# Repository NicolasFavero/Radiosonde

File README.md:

# Radiossonda Experimental (v2.0)

## Sobre o projeto

A **versão 2.0** consiste no desenvolvimento de uma plataforma embarcada para uma **radiossonda experimental**, destinada à aquisição e transmissão de dados ambientais durante voos em balões de alta altitude.

O sistema é baseado em um **ESP32-S3 Supermini** e possui uma arquitetura modular, permitindo a utilização de diferentes módulos de rádio através da mesma PCB, tornando a plataforma flexível para diferentes aplicações e faixas de frequência.

Além da telemetria, a placa oferece interfaces para sensores e módulos opcionais, permitindo sua adaptação para diferentes experimentos científicos e educacionais.

---

# Objetivos

Desenvolver uma plataforma compacta para aquisição e transmissão de dados ambientais, integrando:

- Localização por GPS;
- Medição de pressão e altitude;
- Comunicação via rádio;
- Alimentação para diferentes configurações de bateria;
- Arquitetura preparada para futuras expansões.

---

# Funcionalidades

## Comunicação

- Suporte para múltiplas famílias de rádios;
- Comunicação LoRa e FSK;
- Compatibilidade com diferentes módulos sem necessidade de uma nova PCB.

## Sensoriamento

- Interface para módulo GPS;
- Barramento I²C para sensores adicionais;
- Suporte opcional ao conversor MAX31865 para sensores RTD.

## Alimentação

- Alimentação por baterias Li-Ion/LiPo de **1S até 3S**;
- Conversor Buck-Boost integrado;
- Conector dedicado para bateria.

---

# Status do projeto

🚧 **Em desenvolvimento**

O hardware e o firmware encontram-se em constante evolução, podendo receber novos sensores, módulos de rádio e funcionalidades.

---

# Hardware

- ESP32-S3 Supermini;
- Conversor Buck-Boost;
- Conector para bateria;
- Barramento I²C;
- Suporte para módulo GPS;
- Suporte opcional ao MAX31865;
- Até dois conectores SMA;
- PCB dedicada.

---

# Software

- C++;
- PlatformIO;
- Arduino Framework.

---

# Ambiente de Desenvolvimento

- IDE: PlatformIO;
- Framework: Arduino;
- Placa alvo: ESP32-S3.

---

# Estrutura do Projeto

```text
Firmware/
├── include/
├── lib/
├── src/
└── platformio.ini

Hardware/
├── PCB/
└── Documentação/
```

---

# Aplicação

Projeto desenvolvido para fins educacionais e experimentais, servindo como plataforma para estudos de telemetria, sensoriamento ambiental, comunicação por rádio e sistemas embarcados aplicados a radiossondas.

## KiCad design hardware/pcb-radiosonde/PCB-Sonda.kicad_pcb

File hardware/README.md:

# Hardware

Esta pasta contém os esquemáticos, layouts e demais arquivos relacionados à PCB da **Radiossonda Experimental v2.0**.

A placa foi projetada para oferecer uma plataforma compacta e flexível, permitindo a utilização de diferentes módulos de rádio através da mesma PCB.

---

# Microcontrolador

- ESP32-S3 Supermini

---

# Comunicação por Rádio

A PCB suporta diferentes módulos de rádio.

## Instalação direta

- RF96W;
- RFM95;
- RFM96;
- Outros módulos compatíveis com a mesma pinagem.

## Instalação alternativa

Através da configuração de pads de solda, a PCB também pode utilizar um dos seguintes módulos:

- Módulos baseados no **Semtech LLCC68** (como os modelos da NiceRF);
- **EBYTE E07-M1101D** (formato ESP-01);
- RFM69W.

Essa abordagem permite reutilizar a mesma PCB para diferentes tecnologias e bandas de operação.

---

# Alimentação

A placa possui:

- Conversor Buck-Boost integrado;
- Alimentação por baterias Li-Ion/LiPo de **1S até 3S**;
- Conector dedicado para bateria.

---

# Sensores e Expansões

A PCB disponibiliza:

- Barramento I²C para conexão de sensores, como o BMP280;
- Suporte para módulo GPS;
- Suporte opcional ao conversor **MAX31865** para sensores RTD;
- Conector I²C para expansão de outros periféricos.

Os módulos GPS e MAX31865 podem ser montados na região lateral da placa, permanecendo parcialmente externos ao contorno principal da PCB para otimizar o aproveitamento de espaço.

---

# Antenas

A placa possui suporte para até **2 conectores SMA**, permitindo diferentes configurações de antenas conforme a aplicação.

---

# Estrutura

```text
Hardware/
└── PCB/
```

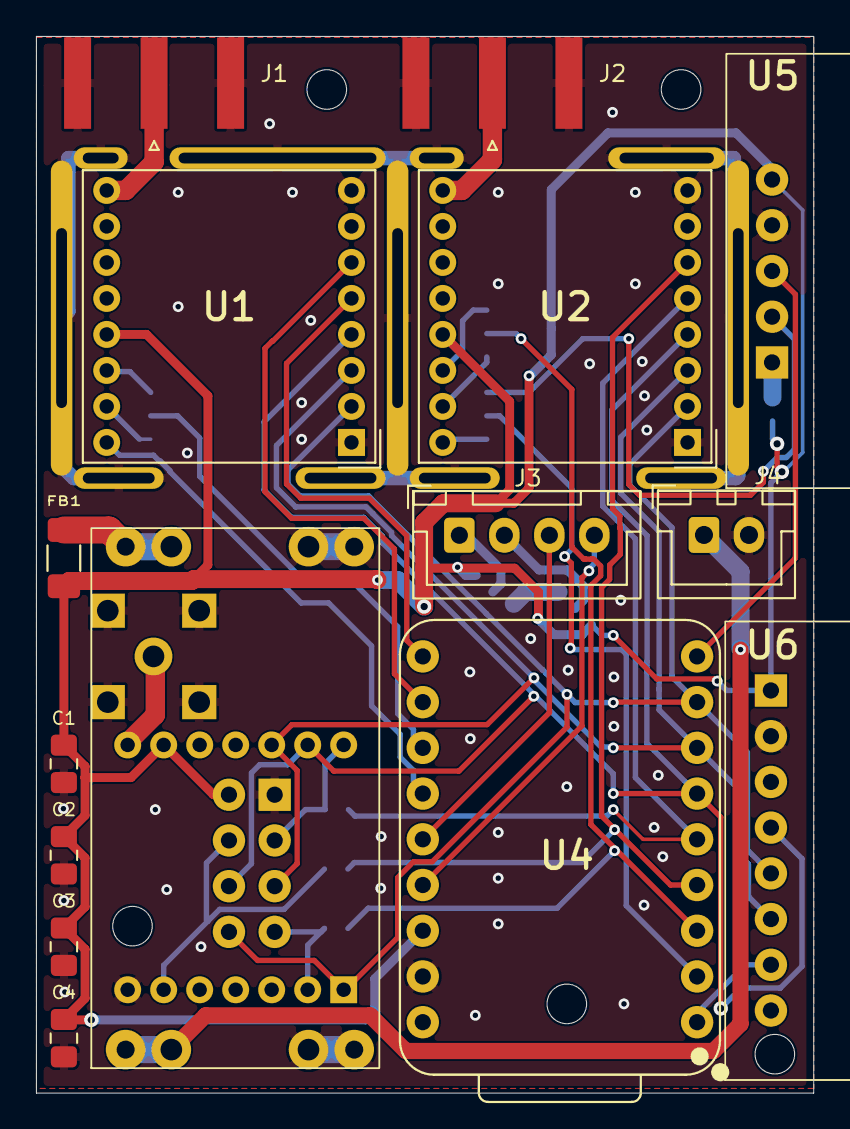
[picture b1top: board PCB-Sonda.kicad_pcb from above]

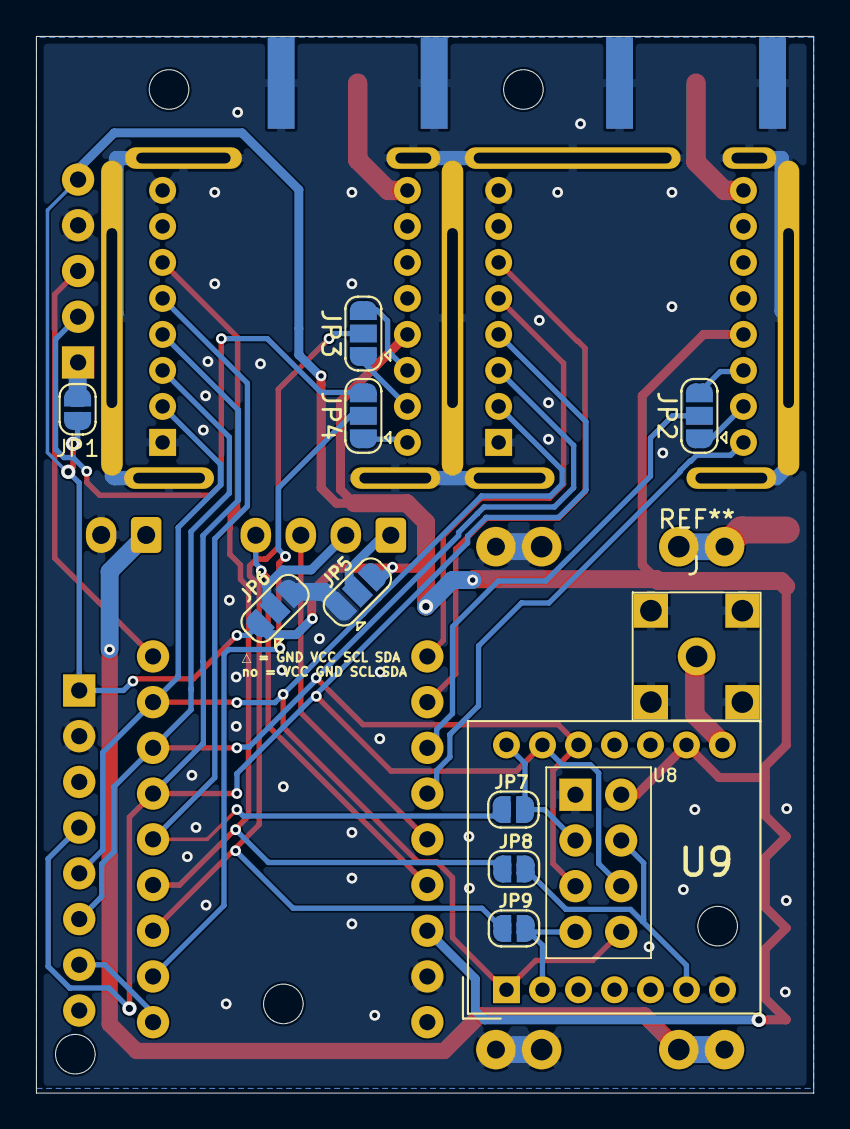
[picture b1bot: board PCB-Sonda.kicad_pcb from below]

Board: 2 copper layers, 43.2 x 58.7 mm, 26 parts (11 on the bottom side), 33 nets.

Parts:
C1, C2: 100nF; C_0805_2012Metric_Pad1.18x1.45mm_HandSolder
C3: 1uF; C_0805_2012Metric_Pad1.18x1.45mm_HandSolder
C4: 1000uF; C_0805_2012Metric_Pad1.18x1.45mm_HandSolder
FB1: 120R; C_1206_3216Metric_Pad1.33x1.80mm_HandSolder
J1, J2: ANT; SMA_Amphenol_132289_EdgeMount
J3: JST; JST_XH_B4B-XH-A_1x04_P2.50mm_Vertical
J4: JST; JST_XH_B2B-XH-A_1x02_P2.50mm_Vertical
JP1, JP7, JP8, JP9: SolderJumper_2_Open; SolderJumper-2_P1.3mm_Open_RoundedPad1.0x1.5mm
JP2, JP3, JP4, JP5, JP6: SolderJumper_3_Open; SolderJumper-3_P1.3mm_Open_RoundedPad1.0x1.5mm
U1: RF96W; rf96w
U2: CC68; rf96w
U3: TPS63070
U4: ESP32-S3-SUPERMIINI; myEsp32-S3-Mini
U5: GPS(black); GPS-PretoComPPS
U6: MAX31865
U8: E07-M11010; Radio-Esp01
U9: RFM69C; rfm69c

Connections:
+3.3V: C1.1, C2.1, C3.1, C4.1, FB1.2, JP1.2 (B), JP5.3 (B), JP6.1 (A), U1.13 (3V3), U2.13 (3V3), U4.16 (VCC_3V3), U5.5 (VCC), U6.1 (VCC), U8.2 (VCC), U9.9 (3V3)
+3.3VA: FB1.1, U3.3 (VOUT)
BUSY-CC68: JP4.1 (A), U2.16 (DIO2/BUSY)
BUSY-RF96W: U1.16 (DIO2/BUSY), U4.13 (GPIO11)
CLK: U1.4 (SCK), U2.4 (SCK), U4.6 (GPIO4), U6.4 (CLK), U8.6 (CLK), U9.13 (SCK)
CS-CC68: JP7.1 (A), U2.5 (NSS), U4.5 (GPIO3)
CS-E07M11010: JP7.2 (B), U8.3 (NSS), U9.14 (NSS)
CS-MAX31865: U4.1 (TX), U6.7 (CS)
CS-RF96W: U1.5 (NSS), U4.10 (GPIO8)
DIO0-CC68: JP3.3 (B), U2.14 (DIO0)
DIO0-E07M11010: JP9.1 (A), U8.7 (DIO0), U9.2 (DIO0)
DIO0-RF96W: JP2.3 (B), U1.14 (DIO0)
DIO0e1-CC68: JP3.2 (C), JP9.2 (B), U4.3 (GPIO1/D0/A0)
DIO0e1-RF96W: JP2.2 (C), U4.12 (GPIO10)
DIO1-CC68: JP3.1 (A), U2.15 (DIO1)
DIO1-RF96W: JP2.1 (A), U1.15 (DIO1)
GND: C1.2, C2.2, C3.2, C4.2, J1.2 (GND), J2.2 (GND), J4.2 (BAT-), JP5.1 (A), JP6.3 (B), U1.1 (GND), U1.8 (GND), U2.1 (GND), U2.8 (GND), U3.1 (GND), U3.4 (GND), U4.17 (GND), U5.4 (GND), U6.2 (GND), U8.1 (GND), U9.7 (GND)
MISO: U1.2 (MISO), U2.2 (MISO), U4.8 (GPIO6), U6.5 (MISO), U8.8 (MISO), U9.1 (MISO)
MOSI: U1.3 (MOSI), U2.3 (MOSI), U4.7 (GPIO5), U6.6 (MOSI), U8.5 (MOSI), U9.12 (MOSI)
unnamed: J1.1 (ANT), U1.9 (ANT)
unnamed: J2.1 (ANT), U2.9 (ANT)
unnamed: J3.2 (GND), JP6.2 (C)
unnamed: J3.1 (VCC), JP5.2 (C)
unnamed: J4.1 (BAT+), U3.2 (VIN)
unnamed: JP1.1 (A), U5.1 (PPS)
RESET-RFM69C: JP8.2 (B), U8.4 (RST), U9.6 (RESET)
RST-CC68: JP8.1 (A), U2.6 (RESET), U4.4 (GPIO2)
RST-RF96W: U1.6 (RESET), U4.11 (GPIO9)
RX-GPS: JP4.3 (B), U5.2 (RXD)
RX-GPS ou BUSY-CC68: JP4.2 (C), U4.2 (RX)
SCL: J3.3 (SCL), U4.14 (GPIO12)
SDA: J3.4 (SDA), U4.15 (GPIO13)
TX-GPS: U4.9 (GPIO7), U5.3 (TXD)

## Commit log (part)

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2026-01-30 Organizacao e Adicao de esquematico
2026-01-30 aumento de dpi do esquematico
2026-01-31 organizacao em pastas
2026-02-10 code update
